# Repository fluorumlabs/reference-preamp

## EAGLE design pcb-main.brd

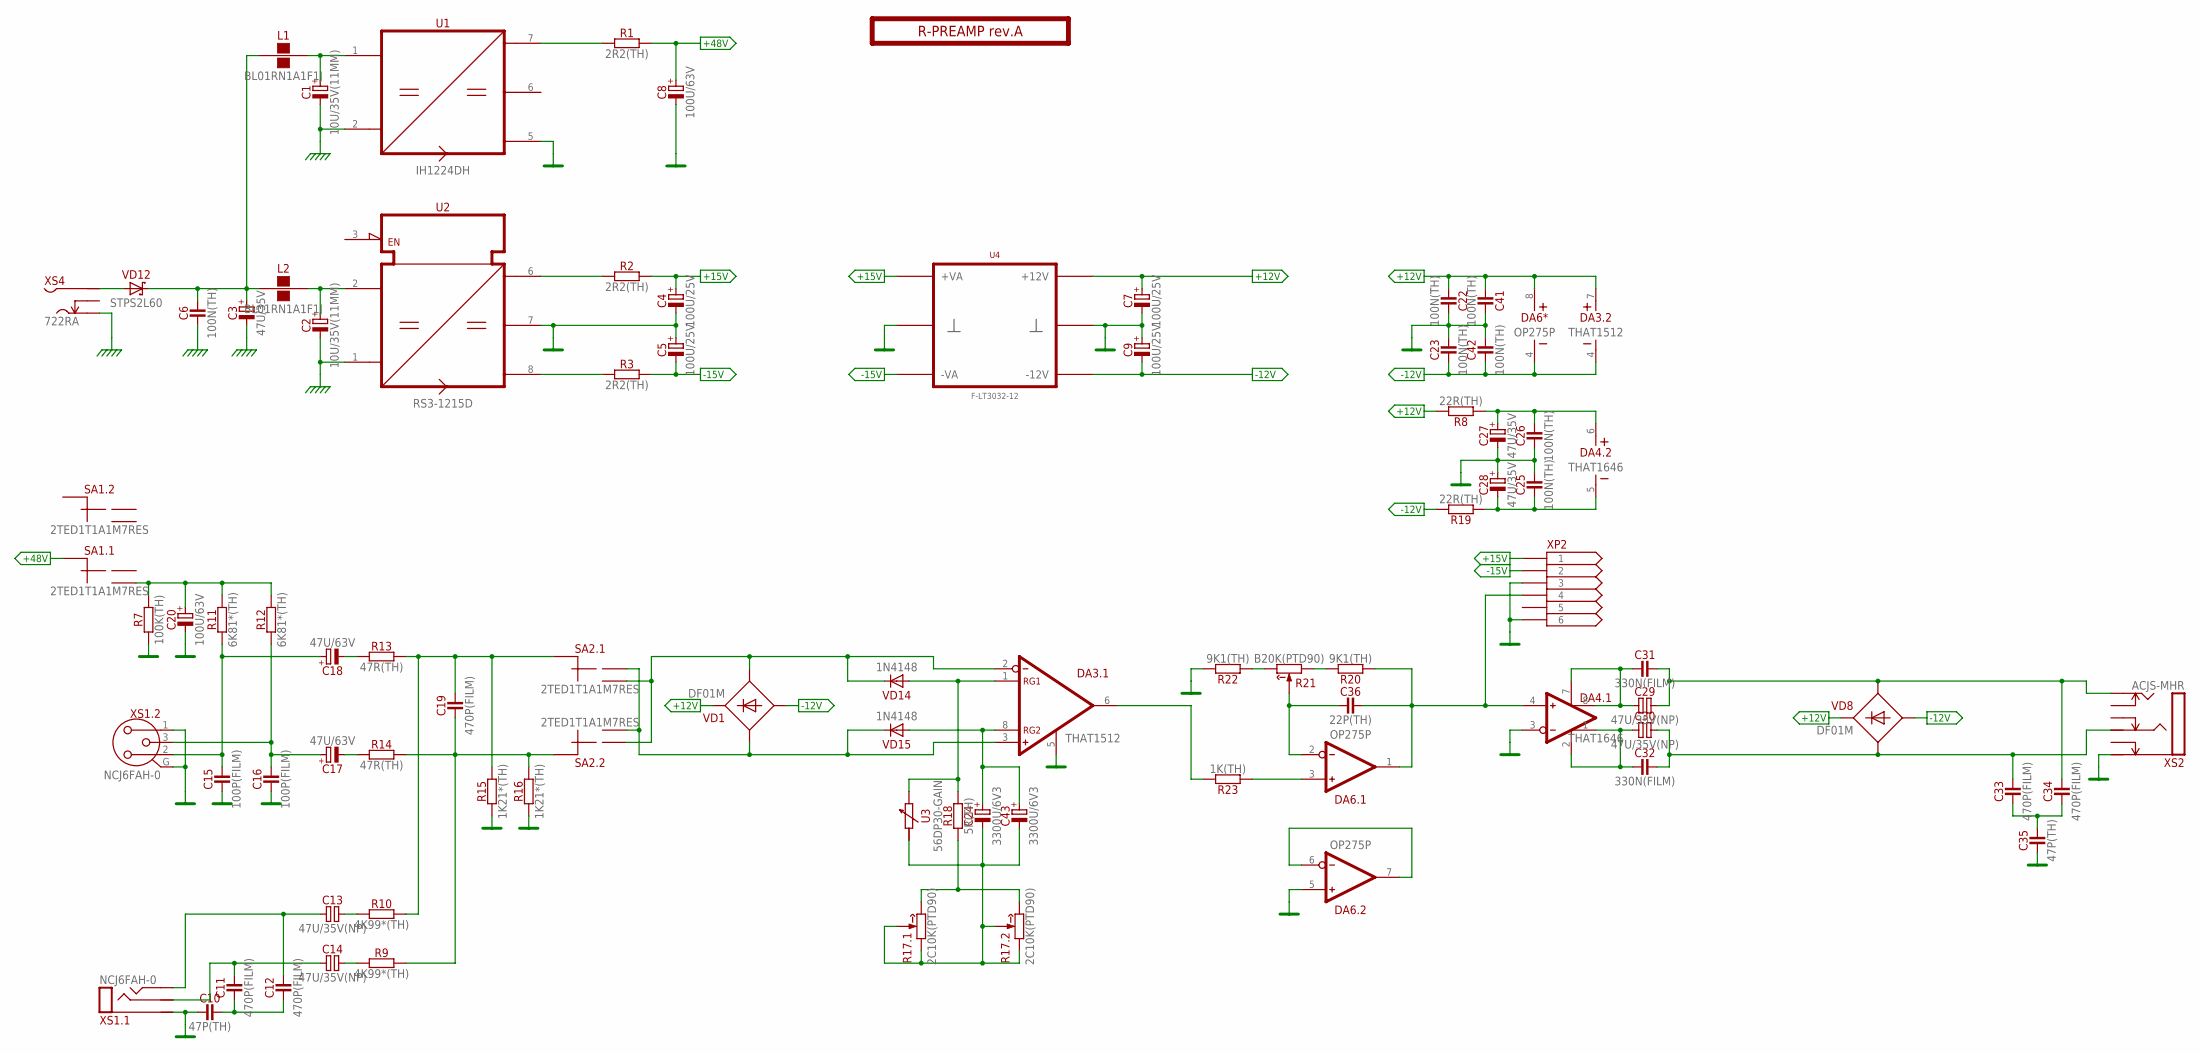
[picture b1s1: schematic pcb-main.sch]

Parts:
C1, C2: 10U/35V(11MM); E2-5
C3, C27, C28: 47U/35V; E2-5
C4, C5, C7, C9: 100U/25V; E2,5-7
C6, C22, C23, C25, C26, C41, C42: 100N(TH); C050-024X044
C8, C20: 100U/63V; E5-10,5
C10, C35: 47P(TH); C050-024X044
C11, C12, C19, C33, C34: 470P(FILM); C050-055X075
C13, C14, C29, C30: 47U/35V(NP); E5-10,5
C15, C16: 100P(FILM); C050-045X075
C17, C18: 47U/63V; E5-10,5
C24, C43: 3300U/6V3; E5-10,5
C31, C32: 330N(FILM); C050-035X075
C36: 22P(TH); C050-024X044
DA3: THAT1512; DIP-8
DA4: THAT1646; DIP-8
DA6: OP275P; DIP-8
L1, L2: BL01RN1A1F1J; BL01RN1A
PCB1: R-PREAMP rev.A; F-LOGO
R1, R2, R3: 2R2(TH); R-0207/10
R7: 100K(TH); R-0207/10
R8, R19: 22R(TH); R-0207/10
R9, R10: 4K99*(TH); R-0207/10
R11, R12: 6K81*(TH); R-0207/10
R13, R14: 47R(TH); R-0207/10
R15, R16: 1K21*(TH); R-0207/10
R17: 2C10K(PTD90); PTD902
R18: 5R(TH); R-0207/10
R20, R22: 9K1(TH); R-0207/10
R21: B20K(PTD90); PTD901
R23: 1K(TH); R-0207/10
SA1, SA2: 2TED1T1A1M7RES
U1: IH1224DH; SIP7
U2: RS3-1215D; SIP8
U3: 56DP30-GAIN; F56DP
U4: F-LT3032-12; F-DIP8-HEATSINK
VD1, VD8: DF01M; MDIP-4
VD12: STPS2L60; DO41-10
VD14, VD15: 1N4148; DO35-7
XP2: CONN-6-NORMAL; MA03-2
XS1: NCJ6FAH-0; NCJ6FA-H-0
XS2: ACJS-MHR; NMJ6HC-S
XS4: 722RA; SWITCHCRAFT-L712RA

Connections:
+12V: C7.+, C22.2, C41.2, DA3.7 (V+), DA6.8 (V+), R8.2, U4.8 (P+12V), VD1.3 (C), VD8.3 (C)
+15V: C4.+, R2.2, U4.1 (P+VA), XP2.1
+48V: C8.+, R1.2, SA1.C1 (CM)
-12V: C9.-, C23.2, C42.2, DA3.4 (V-), DA6.4 (V-), R19.2, U4.5 (P-12V), VD1.4 (A), VD8.4 (A)
-15V: C5.-, R3.2, U4.4 (P-VA), XP2.2
CHASSIS: C1.-, C2.-, C3.-, C6.1, U1.2 (IN-), U2.1 (IN-), XS4.S
GND: C4.-, C5.+, C7.-, C8.-, C9.+, C10.1, C15.1, C16.1, C20.-, C22.1, C23.1, C25.1, C26.2, C27.-, C28.+, C35.1, C41.1, C42.1, DA3.5 (REF), DA4.3 (IN-), DA6.5 (IN+), R7.1, R15.1, R16.1, R22.2, U1.5 (V-), U2.7 (GND), U4.2 (GND1), U4.3 (GND1), U4.6 (GND), U4.7 (GND), XP2.3, XP2.6, XS1.1, XS1.G, XS1.S, XS2.S
unnamed: C2.+, L2.2, U2.2 (IN+)
unnamed: VD12.A, XS4.P
unnamed: C1.+, L1.2, U1.1 (IN+)
unnamed: C13.-, R10.1
unnamed: C3.+, C6.2, L1.1, L2.1, VD12.C
unnamed: C10.2, C11.1, C12.1
unnamed: R1.1, U1.7 (V+)
unnamed: R2.1, U2.6 (V+)
unnamed: R3.1, U2.8 (V-)
unnamed: C11.2, C14.+, XS1.R
unnamed: C12.2, C13.+, XS1.T1 (T), XS1.T2 (T)
unnamed: C14.-, R9.1
unnamed: C15.2, C18.+, R11.1, XS1.2
unnamed: C16.2, C17.+, R12.1, XS1.3
unnamed: C26.1, C27.+, DA4.6 (V+), R8.1
unnamed: C18.-, R13.1
unnamed: C17.-, R14.1
unnamed: DA3.2 (IN-), SA2.NC2 (1), SA2.NO1 (2), VD1.2 (AC2), VD14.C
unnamed: DA3.3 (IN+), SA2.NC1 (1), SA2.NO2 (2), VD1.1 (AC1), VD15.C
unnamed: C24.-, C43.-, R17.A1 (CCW), R17.A2 (W), R17.B1 (CCW), R17.B2 (W), U3.1 (A), U3.2 (A)
unnamed: C25.2, C28.-, DA4.5 (V-), R19.1
unnamed: C20.+, R7.2, R11.2, R12.2, SA1.NO1 (2)
unnamed: C29.+, C31.1, DA4.7 (SENS+), DA4.8 (OUT+)
unnamed: R17.A3 (CW), R17.B3 (CW), R18.1
unnamed: DA3.1 (RG1), R18.2, U3.3 (E), U3.4 (E), VD14.A
unnamed: C24.+, C43.+, DA3.8 (RG2), VD15.A
unnamed: C30.+, C32.1, DA4.1 (OUT-), DA4.2 (SENS-)
unnamed: C29.-, C31.2, C34.2, VD8.1 (AC1), XS2.T
unnamed: C30.-, C32.2, C33.2, VD8.2 (AC2), XS2.R
unnamed: C33.1, C34.1, C35.2
unnamed: C19.2, R10.2, R13.2, R15.2, SA2.C1 (CM)
unnamed: C19.1, R9.2, R14.2, R16.2, SA2.C2 (CM)
unnamed: DA6.6 (IN-), DA6.7 (OUT)
unnamed: DA6.3 (IN+), R23.1
unnamed: C36.1, DA6.2 (IN-), R21.2 (W)
unnamed: R21.3 (CW), R22.1
unnamed: R20.2, R21.1 (CCW)
unnamed: C36.2, DA4.4 (IN+), DA6.1 (OUT), R20.1, XP2.4
unnamed: DA3.6 (OUT), R23.2

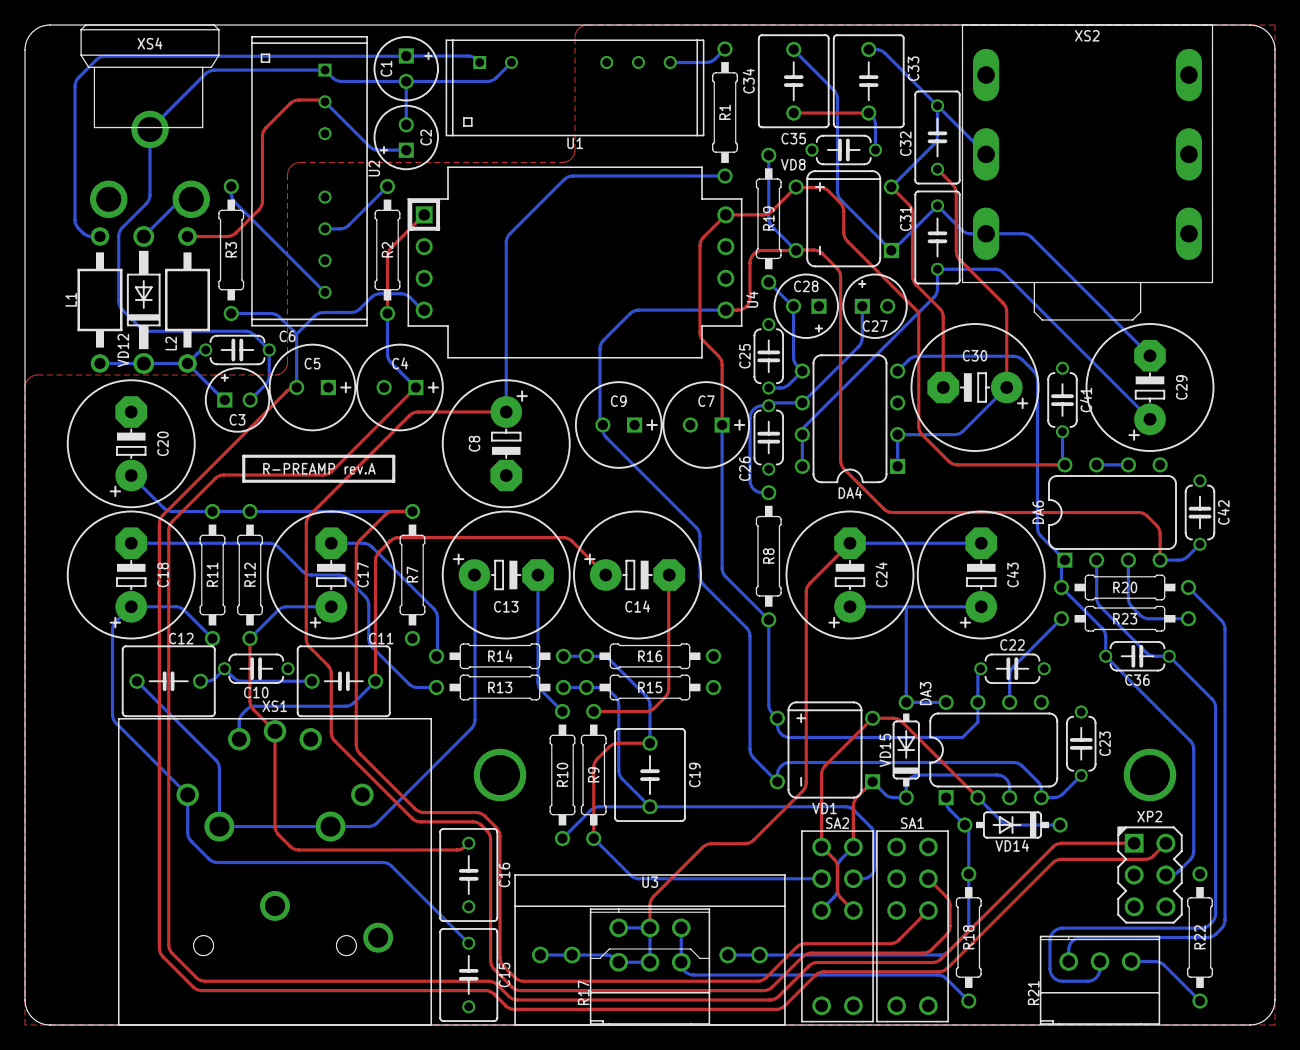
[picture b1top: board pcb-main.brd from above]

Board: 2 copper layers, 100.0 x 80.0 mm, 80 parts (0 on the bottom side), 46 nets.

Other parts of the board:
E$1: B*-080

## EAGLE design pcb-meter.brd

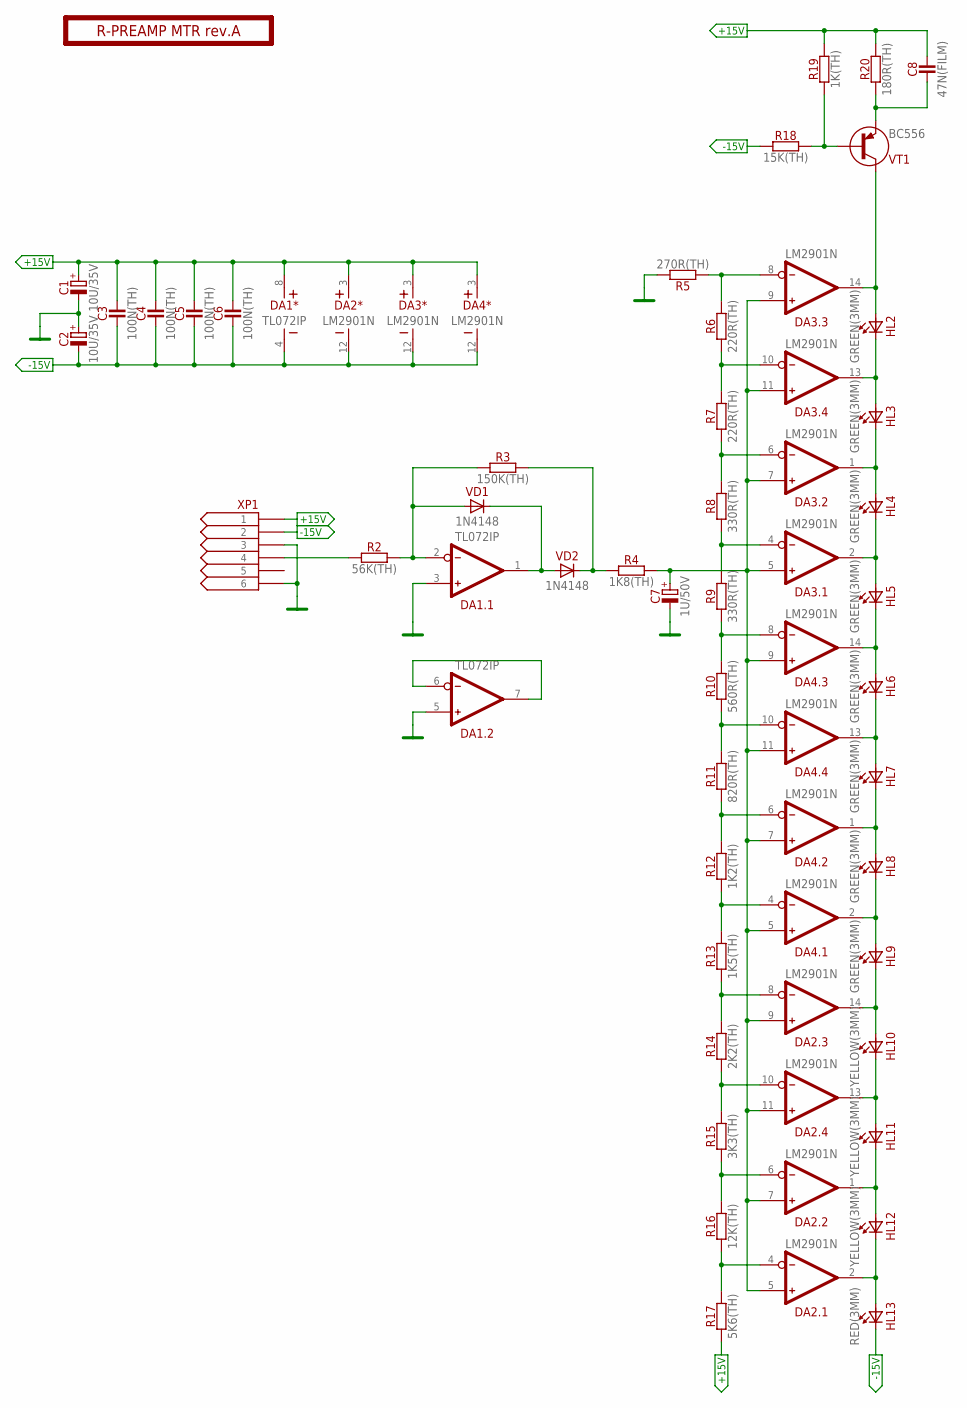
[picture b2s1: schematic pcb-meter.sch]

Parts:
C1, C2: 10U/35V; E2-5
C3, C4, C5, C6: 100N(TH); C050-024X044
C7: 1U/50V; E1,5-4
C8: 47N(FILM); C050-025X075
DA1: TL072IP; DIP-8
DA2, DA3, DA4: LM2901N; DIP-14
HL2, HL3, HL4, HL5, HL6, HL7, HL8, HL9: GREEN(3MM); LED3MM-H
HL10, HL11, HL12: YELLOW(3MM); LED3MM-H
HL13: RED(3MM); LED3MM-H
PCB1: R-PREAMP MTR rev.A; F-LOGO
R2: 56K(TH); R-0207/10
R3: 150K(TH); R-0207/10
R4: 1K8(TH); R-0207/10
R5: 270R(TH); R-0207/10
R6, R7: 220R(TH); R-0207/10
R8, R9: 330R(TH); R-0207/10
R10: 560R(TH); R-0207/10
R11: 820R(TH); R-0207/10
R12: 1K2(TH); R-0207/10
R13: 1K5(TH); R-0207/10
R14: 2K2(TH); R-0207/10
R15: 3K3(TH); R-0207/10
R16: 12K(TH); R-0207/10
R17: 5K6(TH); R-0207/10
R18: 15K(TH); R-0207/10
R19: 1K(TH); R-0207/10
R20: 180R(TH); R-0207/10
VD1, VD2: 1N4148; DO35-7
VT1: BC556; TO92
XP1: CONN-6-NORMAL; MA03-2

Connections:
+15V: C1.+, C3.2, C4.2, C5.2, C6.2, C8.2, DA1.8 (V+), DA2.3 (V+), DA3.3 (V+), DA4.3 (V+), R17.1, R19.2, R20.2, XP1.1
-15V: C2.-, C3.1, C4.1, C5.1, C6.1, DA1.4 (V-), DA2.12 (V-), DA3.12 (V-), DA4.12 (V-), HL13.K (C), R18.1, XP1.2
GND: C1.-, C2.+, C7.-, DA1.3 (IN+), DA1.5 (IN+), R5.2, XP1.3, XP1.6
unnamed: R2.1, XP1.4
unnamed: DA1.2 (IN-), R2.2, R3.1, VD1.A
unnamed: R18.2, R19.1, VT1.2 (B)
unnamed: DA1.1 (OUT), VD1.C, VD2.A
unnamed: R3.2, R4.1, VD2.C
unnamed: C8.1, R20.1, VT1.3 (E)
unnamed: DA2.4 (IN-), R16.1, R17.2
unnamed: DA2.6 (IN-), R15.1, R16.2
unnamed: DA2.10 (IN-), R14.1, R15.2
unnamed: DA2.2 (OUT), HL12.K (C), HL13.A
unnamed: DA2.1 (OUT), HL11.K (C), HL12.A
unnamed: DA2.13 (OUT), HL10.K (C), HL11.A
unnamed: DA2.14 (OUT), HL9.K (C), HL10.A
unnamed: DA4.2 (OUT), HL8.K (C), HL9.A
unnamed: DA4.1 (OUT), HL7.K (C), HL8.A
unnamed: DA4.13 (OUT), HL6.K (C), HL7.A
unnamed: DA4.14 (OUT), HL5.K (C), HL6.A
unnamed: DA3.2 (OUT), HL4.K (C), HL5.A
unnamed: DA3.1 (OUT), HL3.K (C), HL4.A
unnamed: DA3.13 (OUT), HL2.K (C), HL3.A
unnamed: DA3.14 (OUT), HL2.A, VT1.1 (C)
unnamed: C7.+, DA2.5 (IN+), DA2.7 (IN+), DA2.9 (IN+), DA2.11 (IN+), DA3.5 (IN+), DA3.7 (IN+), DA3.9 (IN+), DA3.11 (IN+), DA4.5 (IN+), DA4.7 (IN+), DA4.9 (IN+), DA4.11 (IN+), R4.2
unnamed: DA2.8 (IN-), R13.1, R14.2
unnamed: DA4.4 (IN-), R12.1, R13.2
unnamed: DA4.6 (IN-), R11.1, R12.2
unnamed: DA4.10 (IN-), R10.1, R11.2
unnamed: DA4.8 (IN-), R9.1, R10.2
unnamed: DA3.4 (IN-), R8.1, R9.2
unnamed: DA3.6 (IN-), R7.1, R8.2
unnamed: DA3.10 (IN-), R6.1, R7.2
unnamed: DA3.8 (IN-), R5.1, R6.2
unnamed: DA1.6 (IN-), DA1.7 (OUT)

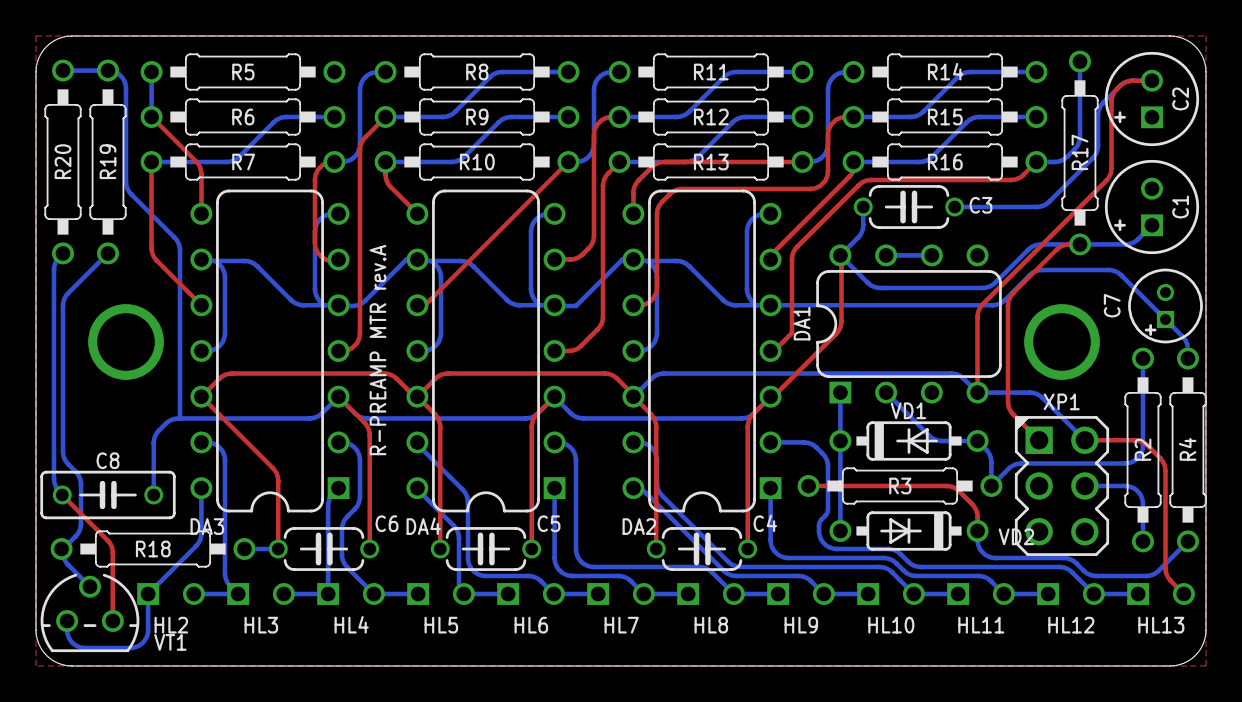
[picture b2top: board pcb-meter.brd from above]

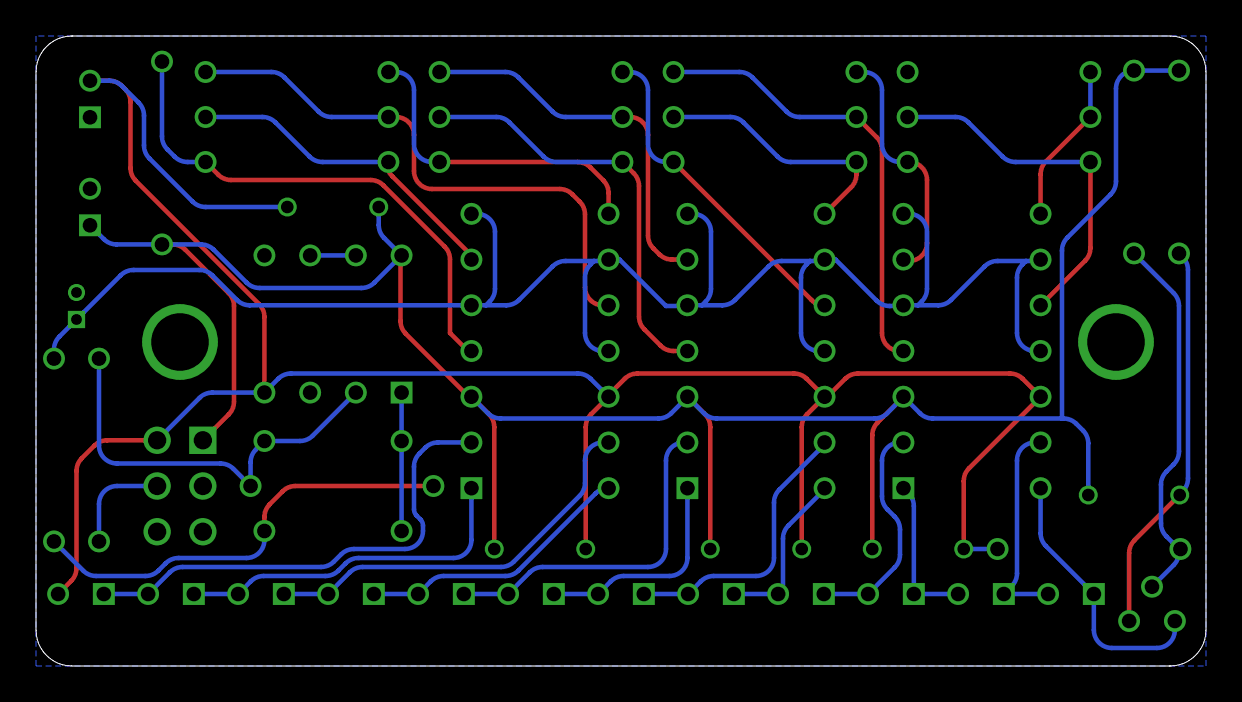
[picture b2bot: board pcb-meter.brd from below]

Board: 2 copper layers, 65.0 x 35.0 mm, 48 parts (12 on the bottom side), 35 nets.

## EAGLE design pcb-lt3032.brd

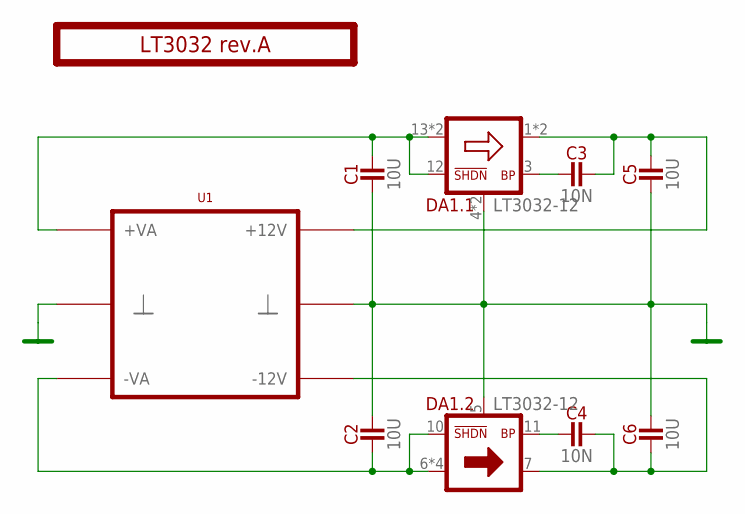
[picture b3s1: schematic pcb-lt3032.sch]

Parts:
C1, C2, C5, C6: 10U; C-1206
C3, C4: 10N; C-0805
DA1: LT3032-12; DE14MA
PCB1: LT3032 rev.A; F-LOGO
U1: F-DUAL-SUPPLY-BOARD; F-DIP8-HEATSINK-NOSILK

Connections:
BYPN: C4.1, DA1.11 (BYP)
BYPP: C3.1, DA1.3 (BYP)
GND: C1.1, C2.2, C5.1, C6.2, DA1.4 (GND), DA1.5 (GND), DA1.15 (GND), U1.2 (GND1), U1.3 (GND1), U1.6 (GND), U1.7 (GND), U1.P$1 (GND)
INN: C2.1, DA1.6 (IN), DA1.8 (IN), DA1.9 (IN), DA1.10 (!SHDN), DA1.16 (IN), U1.4 (P-VA)
INP: C1.2, DA1.12 (!SHDN), DA1.13 (IN), DA1.14 (IN), U1.1 (P+VA)
OUTN: C4.2, C6.1, DA1.7 (OUT), U1.5 (P-12V)
OUTP: C3.2, C5.2, DA1.1 (OUT), DA1.2 (OUT), U1.8 (P+12V)

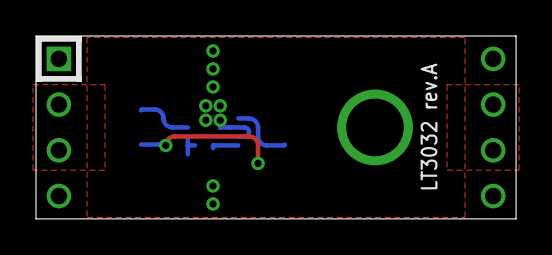
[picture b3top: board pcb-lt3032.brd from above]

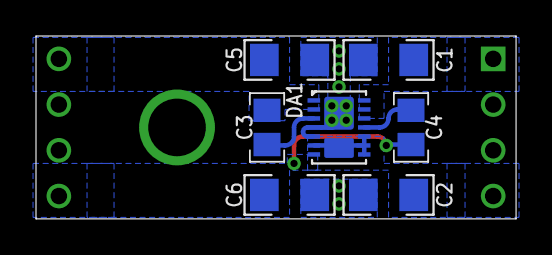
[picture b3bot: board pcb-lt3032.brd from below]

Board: 2 copper layers, 26.7 x 10.2 mm, 9 parts (7 on the bottom side), 7 nets.

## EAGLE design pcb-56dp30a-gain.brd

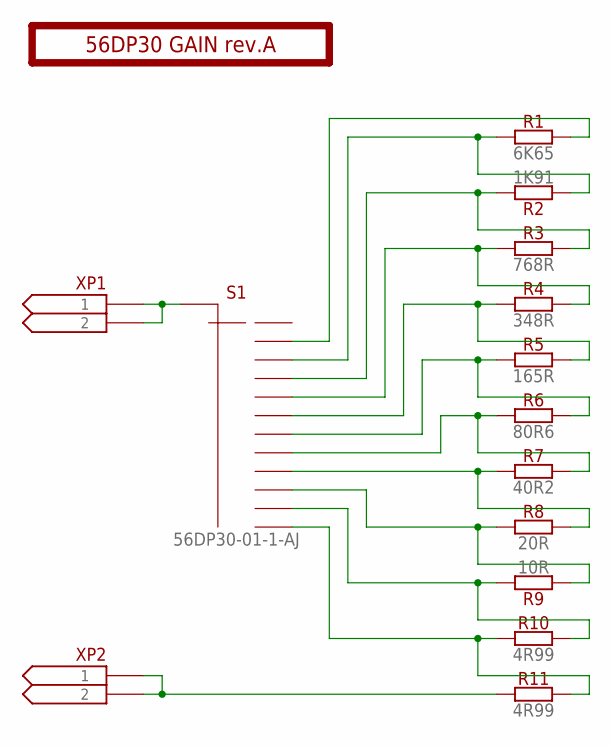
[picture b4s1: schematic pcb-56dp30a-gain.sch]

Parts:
PCB1: 56DP30 GAIN rev.A; F-LOGO
R1: 6K65; R-0805
R2: 1K91; R-0805
R3: 768R; R-0805
R4: 348R; R-0805
R5: 165R; R-0805
R6: 80R6; R-0805
R7: 40R2; R-0805
R8: 20R; R-0805
R9: 10R; R-0805
R10, R11: 4R99; R-0805
S1: 56DP30-01-1-AJ; 56DP30-01-1
XP1, XP2: CONN-2-NORMAL; ML2

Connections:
unnamed: R10.1, R11.2, S1.12
unnamed: R9.2, R10.2, S1.11
unnamed: R8.1, R9.1, S1.10
unnamed: R7.1, R8.2, S1.9
unnamed: R6.1, R7.2, S1.8
unnamed: R5.1, R6.2, S1.7
unnamed: R4.1, R5.2, S1.6
unnamed: R3.1, R4.2, S1.5
unnamed: R2.2, R3.2, S1.4
unnamed: R1.1, R2.1, S1.3
unnamed: R11.1, XP2.1, XP2.2
unnamed: R1.2, S1.2
unnamed: S1.C (CM), XP1.1, XP1.2

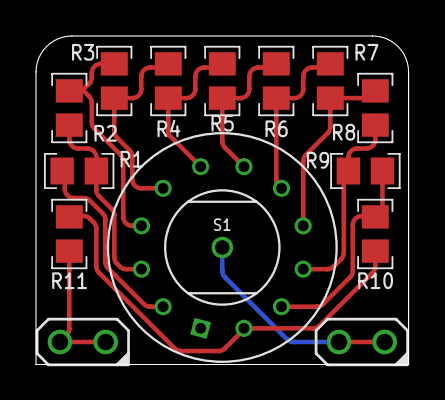
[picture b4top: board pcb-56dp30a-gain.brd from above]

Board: 2 copper layers, 20.7 x 18.2 mm, 15 parts (1 on the bottom side), 13 nets.

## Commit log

2017-02-13 Renumber pcb-meter
2017-02-14 Rename adapter -> pcb
    + Change mounting hole position for pcb-lt3032
2017-02-14 Switch footprint fix
2017-02-14 Remove PP indicator
2017-02-14 Round pcb edges for pcb-meter
2017-03-01 Add 56DP30A-GAIN board
2017-03-01 Add LT3032 Board
2017-03-01 Add Meter Board
2017-03-01 Main Board
2017-03-01 Add component value for LT3032-12 module
2017-03-02 Change DC Connector
2017-03-08 PCB Routing
2017-03-17 Change 20R -> 22R
2017-03-17 Change meter PCB size
2017-03-20 Change LED/front panel spacing
2017-06-21 Update switch footprint
2020-12-02 Add .whitesource configuration file
